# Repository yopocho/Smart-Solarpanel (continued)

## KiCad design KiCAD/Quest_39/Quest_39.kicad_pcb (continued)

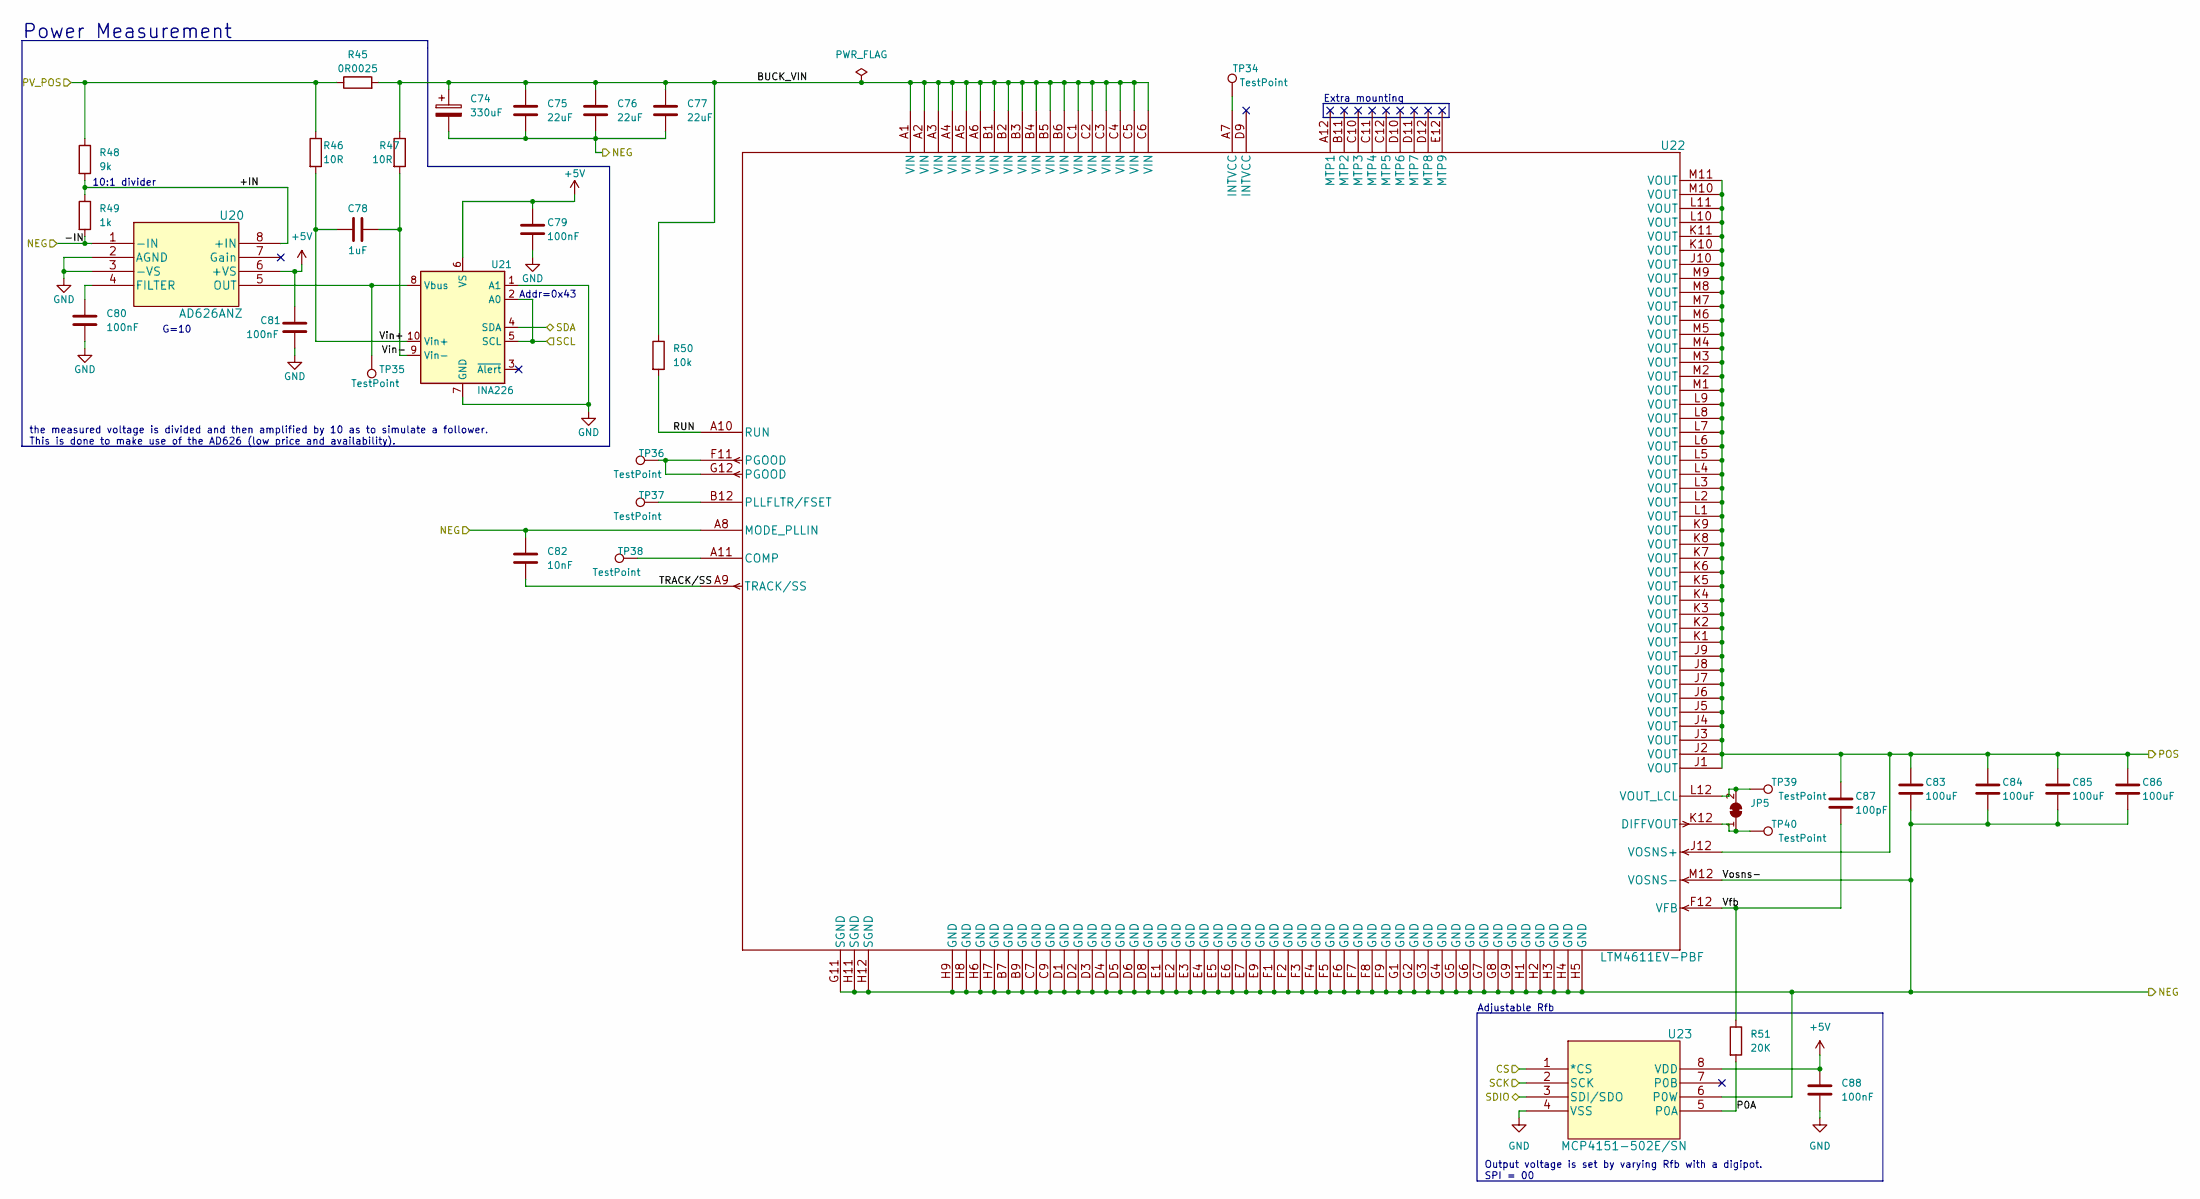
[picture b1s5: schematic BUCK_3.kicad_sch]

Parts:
C74: 330uF; CP_Elec_8x6.9
C75, C76, C77: 22uF; C_0805_2012Metric
C78: 1uF; C_0603_1608Metric
C79, C80, C81, C88: 100nF; C_0603_1608Metric
C82: 10nF; C_0603_1608Metric
C83, C84, C85, C86: 100uF; C_1206_3216Metric
C87: 100pF; C_0603_1608Metric
JP5: SolderJumper_2_Bridged; SolderJumper-2_P1.3mm_Bridged_RoundedPad1.0x1.5mm
R45: 0R0025; R_1206_3216Metric
R46, R47: 10R; R_0805_2012Metric
R48: 9k; R_0805_2012Metric
R49: 1k; R_0805_2012Metric
R50: 10k; R_0805_2012Metric
R51: 20K; R_0805_2012Metric
TP34, TP35, TP36, TP37, TP38, TP39, TP40: TestPoint; TestPoint_Pad_D2.0mm
U20: AD626ANZ; DIP-8_W7.62mm_Socket_LongPads
U21: INA226; VSSOP-10_3x3mm_P0.5mm
U22: LTM4611EV-PBF; Linear_LGA-133_15.0x15.0mm_Layout12x12_P1.27mm
U23: MCP4151-502E/SN; MSOP-8_3x3mm_P0.65mm

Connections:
+5V: C79.1, C81.1, C88.1, U20.6 (+VS), U21.6 (VS), U23.8 (VDD); also elsewhere on the board
/BUCK_3/+IN: R48.2, R49.1, U20.8 (+IN)
/BUCK_3/BUCK_VIN: C74.1, C75.1, C76.1, C77.1, R45.2, R47.1, R50.1, U22.A1 (VIN), U22.A2 (VIN), U22.A3 (VIN), U22.A4 (VIN), U22.A5 (VIN), U22.A6 (VIN), U22.B1 (VIN), U22.B2 (VIN), U22.B3 (VIN), U22.B4 (VIN), U22.B5 (VIN), U22.B6 (VIN), U22.C1 (VIN), U22.C2 (VIN), U22.C3 (VIN), U22.C4 (VIN), U22.C5 (VIN), U22.C6 (VIN)
/BUCK_3/P0A: R51.2, U23.5 (P0A)
/BUCK_3/RUN: R50.2, U22.A10 (RUN)
/BUCK_3/TRACK/SS: C82.2, U22.A9 (TRACK/SS)
/BUCK_3/Vfb: C87.2, R51.1, U22.F12 (VFB)
/BUCK_3/Vin+: C78.1, R46.2, U21.10 (Vin+)
/BUCK_3/Vin-: C78.2, R47.2, U21.9 (Vin-)
/CS3: U23.1 (*CS); also elsewhere on the board
/NEG_3: C74.2, C75.2, C76.2, C77.2, C82.1, C83.2, C84.2, C85.2, C86.2, R49.2, U20.1 (-IN), U22.A8 (MODE_PLLIN), U22.B7 (GND), U22.B9 (GND), U22.C7 (GND), U22.C9 (GND), U22.D1 (GND), U22.D2 (GND), U22.D3 (GND), U22.D4 (GND), U22.D5 (GND), U22.D6 (GND), U22.D8 (GND), U22.E1 (GND), U22.E2 (GND), U22.E3 (GND), U22.E4 (GND), U22.E5 (GND), U22.E6 (GND), U22.E7 (GND), U22.E9 (GND), U22.F1 (GND), U22.F2 (GND), U22.F3 (GND), U22.F4 (GND), U22.F5 (GND), U22.F6 (GND), U22.F7 (GND), U22.F8 (GND), U22.F9 (GND), U22.G1 (GND), U22.G2 (GND), U22.G3 (GND), U22.G4 (GND), U22.G5 (GND), U22.G6 (GND), U22.G7 (GND), U22.G8 (GND), U22.G9 (GND), U22.G11 (SGND), U22.H1 (GND), U22.H2 (GND), U22.H3 (GND), U22.H4 (GND), U22.H5 (GND), U22.H6 (GND), U22.H7 (GND), U22.H8 (GND), U22.H9 (GND), U22.H11 (SGND), U22.H12 (SGND), U22.M12 (VOSNS-), U23.6 (P0W); also elsewhere on the board
/NEG_4: C83.1, C84.1, C85.1, C86.1, C87.1, U22.J1 (VOUT), U22.J2 (VOUT), U22.J3 (VOUT), U22.J4 (VOUT), U22.J5 (VOUT), U22.J6 (VOUT), U22.J7 (VOUT), U22.J8 (VOUT), U22.J9 (VOUT), U22.J10 (VOUT), U22.J12 (VOSNS+), U22.K1 (VOUT), U22.K2 (VOUT), U22.K3 (VOUT), U22.K4 (VOUT), U22.K5 (VOUT), U22.K6 (VOUT), U22.K7 (VOUT), U22.K8 (VOUT), U22.K9 (VOUT), U22.K10 (VOUT), U22.K11 (VOUT), U22.L1 (VOUT), U22.L2 (VOUT), U22.L3 (VOUT), U22.L4 (VOUT), U22.L5 (VOUT), U22.L6 (VOUT), U22.L7 (VOUT), U22.L8 (VOUT), U22.L9 (VOUT), U22.L10 (VOUT), U22.L11 (VOUT), U22.M1 (VOUT), U22.M2 (VOUT), U22.M3 (VOUT), U22.M4 (VOUT), U22.M5 (VOUT), U22.M6 (VOUT), U22.M7 (VOUT), U22.M8 (VOUT), U22.M9 (VOUT), U22.M10 (VOUT), U22.M11 (VOUT); also elsewhere on the board
/PV_POS_3: R45.1, R46.1, R48.1; also elsewhere on the board
/SCK: U23.2 (SCK); also elsewhere on the board
/SCL: U21.2 (A0), U21.5 (SCL); also elsewhere on the board
/SDA: U21.4 (SDA); also elsewhere on the board
/SDIO: U23.3 (SDI/SDO); also elsewhere on the board
GND: C79.2, C80.2, C81.2, C88.2, U20.2 (AGND), U20.3 (-VS), U21.1 (A1), U21.7 (GND), U23.4 (VSS); also elsewhere on the board
unnamed: C80.1, U20.4 (FILTER)
unnamed: JP5.1 (A), TP40.1, U22.K12 (DIFFVOUT)
unnamed: JP5.2 (B), TP39.1, U22.L12 (VOUT_LCL)
unnamed: TP34.1, U22.A7 (INTVCC)
unnamed: TP35.1, U20.5 (OUT), U21.8 (Vbus)
unnamed: TP36.1, U22.F11 (PGOOD), U22.G12 (PGOOD)
unnamed: TP37.1, U22.B12 (PLLFLTR/FSET)
unnamed: TP38.1, U22.A11 (COMP)

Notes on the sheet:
Adjustable Rfb
the measured voltage is divided and then amplified by 10 as to simulate a follower. This is done to make use of the AD626 (low price and availability).
Extra mounting
Output voltage is set by varying Rfb with a digipot. SPI = 00
Addr=0x43
10:1 divider
G=10
Power Measurement

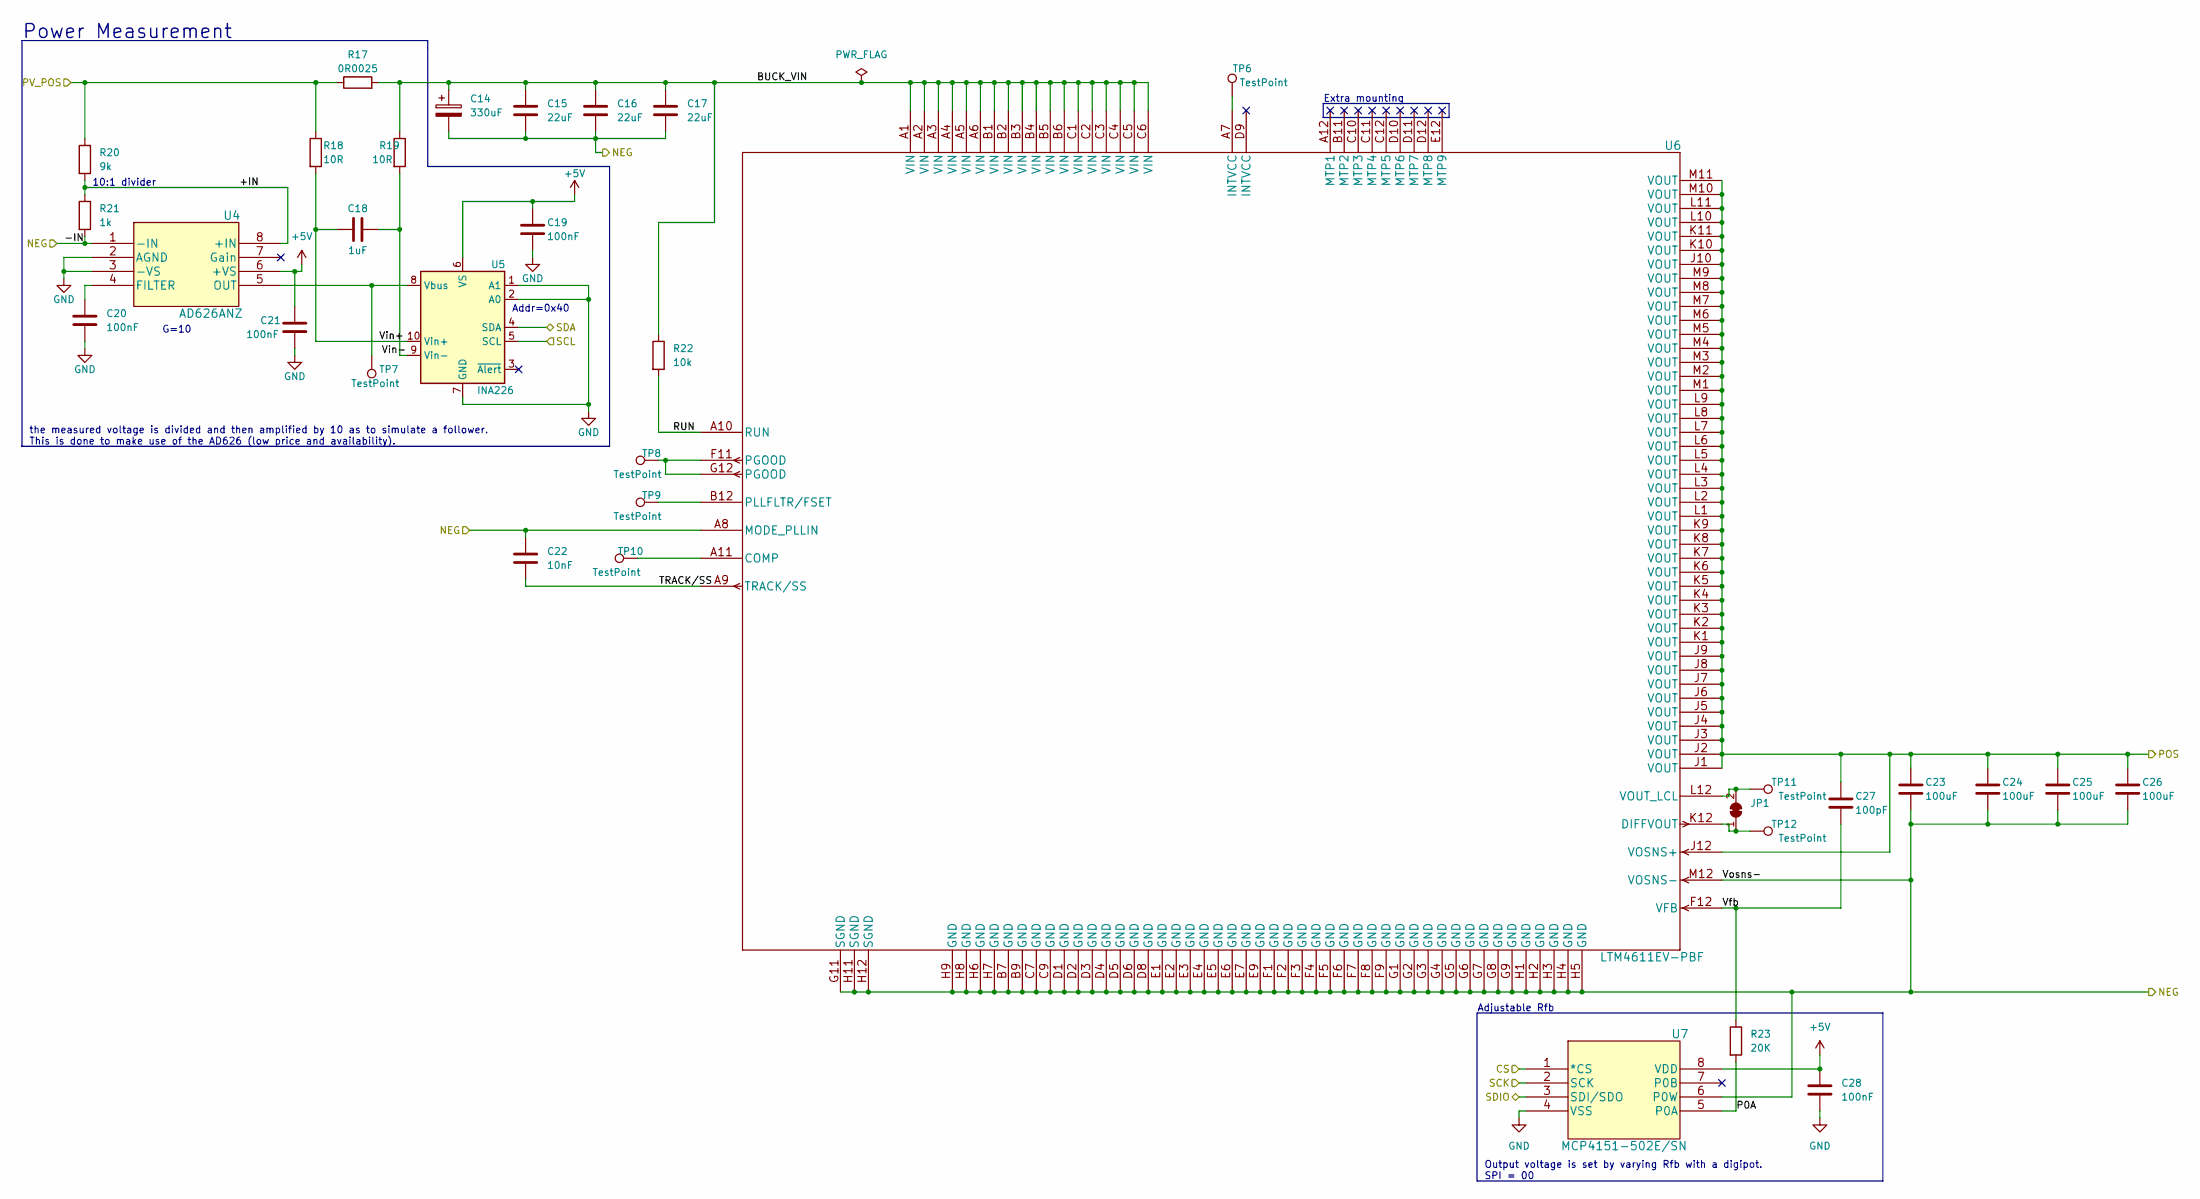
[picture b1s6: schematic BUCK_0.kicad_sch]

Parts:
C14: 330uF; CP_Elec_8x6.9
C15, C16, C17: 22uF; C_0805_2012Metric
C18: 1uF; C_0603_1608Metric
C19, C20, C21, C28: 100nF; C_0603_1608Metric
C22: 10nF; C_0603_1608Metric
C23, C24, C25, C26: 100uF; C_1206_3216Metric
C27: 100pF; C_0603_1608Metric
JP1: SolderJumper_2_Bridged; SolderJumper-2_P1.3mm_Bridged_RoundedPad1.0x1.5mm
R17: 0R0025; R_1206_3216Metric
R18, R19: 10R; R_0805_2012Metric
R20: 9k; R_0805_2012Metric
R21: 1k; R_0805_2012Metric
R22: 10k; R_0805_2012Metric
R23: 20K; R_0805_2012Metric
TP6, TP7, TP8, TP9, TP10, TP11, TP12: TestPoint; TestPoint_Pad_D2.0mm
U4: AD626ANZ; DIP-8_W7.62mm_Socket_LongPads
U5: INA226; VSSOP-10_3x3mm_P0.5mm
U6: LTM4611EV-PBF; Linear_LGA-133_15.0x15.0mm_Layout12x12_P1.27mm
U7: MCP4151-502E/SN; MSOP-8_3x3mm_P0.65mm

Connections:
+5V: C19.1, C21.1, C28.1, U4.6 (+VS), U5.6 (VS), U7.8 (VDD); also elsewhere on the board
/BUCK_0/+IN: R20.2, R21.1, U4.8 (+IN)
/BUCK_0/BUCK_VIN: C14.1, C15.1, C16.1, C17.1, R17.2, R19.1, R22.1, U6.A1 (VIN), U6.A2 (VIN), U6.A3 (VIN), U6.A4 (VIN), U6.A5 (VIN), U6.A6 (VIN), U6.B1 (VIN), U6.B2 (VIN), U6.B3 (VIN), U6.B4 (VIN), U6.B5 (VIN), U6.B6 (VIN), U6.C1 (VIN), U6.C2 (VIN), U6.C3 (VIN), U6.C4 (VIN), U6.C5 (VIN), U6.C6 (VIN)
/BUCK_0/P0A: R23.2, U7.5 (P0A)
/BUCK_0/RUN: R22.2, U6.A10 (RUN)
/BUCK_0/TRACK/SS: C22.2, U6.A9 (TRACK/SS)
/BUCK_0/Vfb: C27.2, R23.1, U6.F12 (VFB)
/BUCK_0/Vin+: C18.2, R18.2, U5.10 (Vin+)
/BUCK_0/Vin-: C18.1, R19.2, U5.9 (Vin-)
/CS0: U7.1 (*CS); also elsewhere on the board
/NEG_0: C14.2, C15.2, C16.2, C17.2, C22.1, C23.2, C24.2, C25.2, C26.2, R21.2, U4.1 (-IN), U6.A8 (MODE_PLLIN), U6.B7 (GND), U6.B9 (GND), U6.C7 (GND), U6.C9 (GND), U6.D1 (GND), U6.D2 (GND), U6.D3 (GND), U6.D4 (GND), U6.D5 (GND), U6.D6 (GND), U6.D8 (GND), U6.E1 (GND), U6.E2 (GND), U6.E3 (GND), U6.E4 (GND), U6.E5 (GND), U6.E6 (GND), U6.E7 (GND), U6.E9 (GND), U6.F1 (GND), U6.F2 (GND), U6.F3 (GND), U6.F4 (GND), U6.F5 (GND), U6.F6 (GND), U6.F7 (GND), U6.F8 (GND), U6.F9 (GND), U6.G1 (GND), U6.G2 (GND), U6.G3 (GND), U6.G4 (GND), U6.G5 (GND), U6.G6 (GND), U6.G7 (GND), U6.G8 (GND), U6.G9 (GND), U6.G11 (SGND), U6.H1 (GND), U6.H2 (GND), U6.H3 (GND), U6.H4 (GND), U6.H5 (GND), U6.H6 (GND), U6.H7 (GND), U6.H8 (GND), U6.H9 (GND), U6.H11 (SGND), U6.H12 (SGND), U6.M12 (VOSNS-), U7.6 (P0W); also elsewhere on the board
/NEG_1: C23.1, C24.1, C25.1, C26.1, C27.1, U6.J1 (VOUT), U6.J2 (VOUT), U6.J3 (VOUT), U6.J4 (VOUT), U6.J5 (VOUT), U6.J6 (VOUT), U6.J7 (VOUT), U6.J8 (VOUT), U6.J9 (VOUT), U6.J10 (VOUT), U6.J12 (VOSNS+), U6.K1 (VOUT), U6.K2 (VOUT), U6.K3 (VOUT), U6.K4 (VOUT), U6.K5 (VOUT), U6.K6 (VOUT), U6.K7 (VOUT), U6.K8 (VOUT), U6.K9 (VOUT), U6.K10 (VOUT), U6.K11 (VOUT), U6.L1 (VOUT), U6.L2 (VOUT), U6.L3 (VOUT), U6.L4 (VOUT), U6.L5 (VOUT), U6.L6 (VOUT), U6.L7 (VOUT), U6.L8 (VOUT), U6.L9 (VOUT), U6.L10 (VOUT), U6.L11 (VOUT), U6.M1 (VOUT), U6.M2 (VOUT), U6.M3 (VOUT), U6.M4 (VOUT), U6.M5 (VOUT), U6.M6 (VOUT), U6.M7 (VOUT), U6.M8 (VOUT), U6.M9 (VOUT), U6.M10 (VOUT), U6.M11 (VOUT); also elsewhere on the board
/PV_POS_0: R17.1, R18.1, R20.1; also elsewhere on the board
/SCK: U7.2 (SCK); also elsewhere on the board
/SCL: U5.5 (SCL); also elsewhere on the board
/SDA: U5.4 (SDA); also elsewhere on the board
/SDIO: U7.3 (SDI/SDO); also elsewhere on the board
GND: C19.2, C20.2, C21.2, C28.2, U4.2 (AGND), U4.3 (-VS), U5.1 (A1), U5.2 (A0), U5.7 (GND), U7.4 (VSS); also elsewhere on the board
unnamed: C20.1, U4.4 (FILTER)
unnamed: JP1.1 (A), TP12.1, U6.K12 (DIFFVOUT)
unnamed: JP1.2 (B), TP11.1, U6.L12 (VOUT_LCL)
unnamed: TP6.1, U6.A7 (INTVCC)
unnamed: TP7.1, U4.5 (OUT), U5.8 (Vbus)
unnamed: TP8.1, U6.F11 (PGOOD), U6.G12 (PGOOD)
unnamed: TP9.1, U6.B12 (PLLFLTR/FSET)
unnamed: TP10.1, U6.A11 (COMP)

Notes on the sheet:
Addr=0x40
10:1 divider
the measured voltage is divided and then amplified by 10 as to simulate a follower. This is done to make use of the AD626 (low price and availability).
Power Measurement
Output voltage is set by varying Rfb with a digipot. SPI = 00
Adjustable Rfb
Extra mounting
G=10

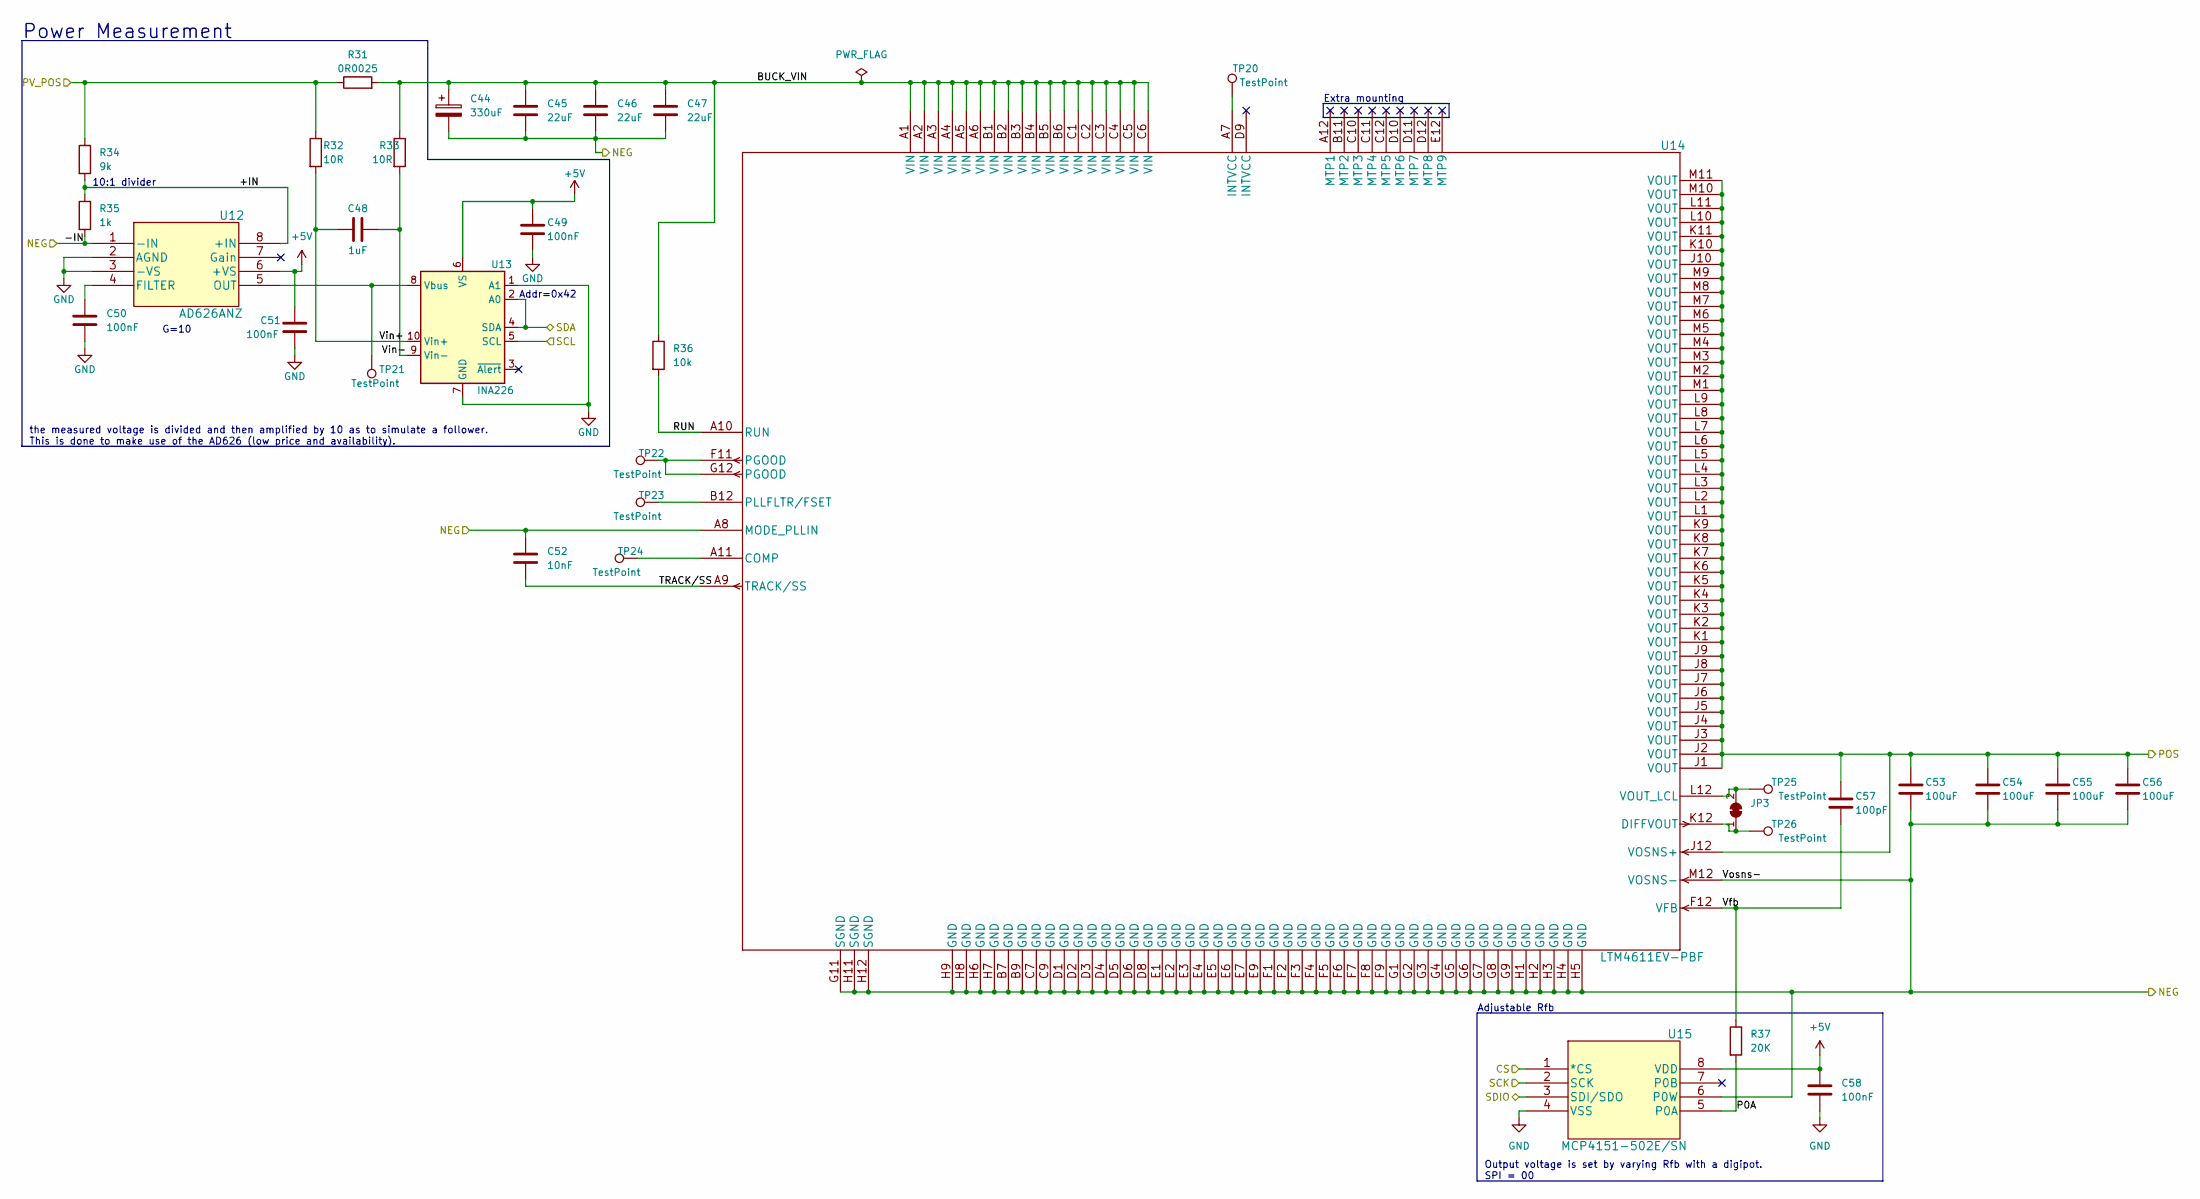
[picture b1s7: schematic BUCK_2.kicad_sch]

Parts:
C44: 330uF; CP_Elec_8x6.9
C45, C46, C47: 22uF; C_0805_2012Metric
C48: 1uF; C_0603_1608Metric
C49, C50, C51, C58: 100nF; C_0603_1608Metric
C52: 10nF; C_0603_1608Metric
C53, C54, C55, C56: 100uF; C_1206_3216Metric
C57: 100pF; C_0603_1608Metric
JP3: SolderJumper_2_Bridged; SolderJumper-2_P1.3mm_Bridged_RoundedPad1.0x1.5mm
R31: 0R0025; R_1206_3216Metric
R32, R33: 10R; R_0805_2012Metric
R34: 9k; R_0805_2012Metric
R35: 1k; R_0805_2012Metric
R36: 10k; R_0805_2012Metric
R37: 20K; R_0805_2012Metric
TP20, TP21, TP22, TP23, TP24, TP25, TP26: TestPoint; TestPoint_Pad_D2.0mm
U12: AD626ANZ; DIP-8_W7.62mm_Socket_LongPads
U13: INA226; VSSOP-10_3x3mm_P0.5mm
U14: LTM4611EV-PBF; Linear_LGA-133_15.0x15.0mm_Layout12x12_P1.27mm
U15: MCP4151-502E/SN; MSOP-8_3x3mm_P0.65mm

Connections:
+5V: C49.1, C51.1, C58.1, U12.6 (+VS), U13.6 (VS), U15.8 (VDD); also elsewhere on the board
/BUCK_2/+IN: R34.2, R35.1, U12.8 (+IN)
/BUCK_2/BUCK_VIN: C44.1, C45.1, C46.1, C47.1, R31.2, R33.1, R36.1, U14.A1 (VIN), U14.A2 (VIN), U14.A3 (VIN), U14.A4 (VIN), U14.A5 (VIN), U14.A6 (VIN), U14.B1 (VIN), U14.B2 (VIN), U14.B3 (VIN), U14.B4 (VIN), U14.B5 (VIN), U14.B6 (VIN), U14.C1 (VIN), U14.C2 (VIN), U14.C3 (VIN), U14.C4 (VIN), U14.C5 (VIN), U14.C6 (VIN)
/BUCK_2/P0A: R37.2, U15.5 (P0A)
/BUCK_2/RUN: R36.2, U14.A10 (RUN)
/BUCK_2/TRACK/SS: C52.2, U14.A9 (TRACK/SS)
/BUCK_2/Vfb: C57.2, R37.1, U14.F12 (VFB)
/BUCK_2/Vin+: C48.1, R32.2, U13.10 (Vin+)
/BUCK_2/Vin-: C48.2, R33.2, U13.9 (Vin-)
/CS2: U15.1 (*CS); also elsewhere on the board
/NEG_2: C44.2, C45.2, C46.2, C47.2, C52.1, C53.2, C54.2, C55.2, C56.2, R35.2, U12.1 (-IN), U14.A8 (MODE_PLLIN), U14.B7 (GND), U14.B9 (GND), U14.C7 (GND), U14.C9 (GND), U14.D1 (GND), U14.D2 (GND), U14.D3 (GND), U14.D4 (GND), U14.D5 (GND), U14.D6 (GND), U14.D8 (GND), U14.E1 (GND), U14.E2 (GND), U14.E3 (GND), U14.E4 (GND), U14.E5 (GND), U14.E6 (GND), U14.E7 (GND), U14.E9 (GND), U14.F1 (GND), U14.F2 (GND), U14.F3 (GND), U14.F4 (GND), U14.F5 (GND), U14.F6 (GND), U14.F7 (GND), U14.F8 (GND), U14.F9 (GND), U14.G1 (GND), U14.G2 (GND), U14.G3 (GND), U14.G4 (GND), U14.G5 (GND), U14.G6 (GND), U14.G7 (GND), U14.G8 (GND), U14.G9 (GND), U14.G11 (SGND), U14.H1 (GND), U14.H2 (GND), U14.H3 (GND), U14.H4 (GND), U14.H5 (GND), U14.H6 (GND), U14.H7 (GND), U14.H8 (GND), U14.H9 (GND), U14.H11 (SGND), U14.H12 (SGND), U14.M12 (VOSNS-), U15.6 (P0W); also elsewhere on the board
/NEG_3: C53.1, C54.1, C55.1, C56.1, C57.1, U14.J1 (VOUT), U14.J2 (VOUT), U14.J3 (VOUT), U14.J4 (VOUT), U14.J5 (VOUT), U14.J6 (VOUT), U14.J7 (VOUT), U14.J8 (VOUT), U14.J9 (VOUT), U14.J10 (VOUT), U14.J12 (VOSNS+), U14.K1 (VOUT), U14.K2 (VOUT), U14.K3 (VOUT), U14.K4 (VOUT), U14.K5 (VOUT), U14.K6 (VOUT), U14.K7 (VOUT), U14.K8 (VOUT), U14.K9 (VOUT), U14.K10 (VOUT), U14.K11 (VOUT), U14.L1 (VOUT), U14.L2 (VOUT), U14.L3 (VOUT), U14.L4 (VOUT), U14.L5 (VOUT), U14.L6 (VOUT), U14.L7 (VOUT), U14.L8 (VOUT), U14.L9 (VOUT), U14.L10 (VOUT), U14.L11 (VOUT), U14.M1 (VOUT), U14.M2 (VOUT), U14.M3 (VOUT), U14.M4 (VOUT), U14.M5 (VOUT), U14.M6 (VOUT), U14.M7 (VOUT), U14.M8 (VOUT), U14.M9 (VOUT), U14.M10 (VOUT), U14.M11 (VOUT); also elsewhere on the board
/PV_POS_2: R31.1, R32.1, R34.1; also elsewhere on the board
/SCK: U15.2 (SCK); also elsewhere on the board
/SCL: U13.5 (SCL); also elsewhere on the board
/SDA: U13.2 (A0), U13.4 (SDA); also elsewhere on the board
/SDIO: U15.3 (SDI/SDO); also elsewhere on the board
GND: C49.2, C50.2, C51.2, C58.2, U12.2 (AGND), U12.3 (-VS), U13.1 (A1), U13.7 (GND), U15.4 (VSS); also elsewhere on the board
unnamed: C50.1, U12.4 (FILTER)
unnamed: JP3.1 (A), TP26.1, U14.K12 (DIFFVOUT)
unnamed: JP3.2 (B), TP25.1, U14.L12 (VOUT_LCL)
unnamed: TP20.1, U14.A7 (INTVCC)
unnamed: TP21.1, U12.5 (OUT), U13.8 (Vbus)
unnamed: TP22.1, U14.F11 (PGOOD), U14.G12 (PGOOD)
unnamed: TP23.1, U14.B12 (PLLFLTR/FSET)
unnamed: TP24.1, U14.A11 (COMP)

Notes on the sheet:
the measured voltage is divided and then amplified by 10 as to simulate a follower. This is done to make use of the AD626 (low price and availability).
Extra mounting
G=10
10:1 divider
Adjustable Rfb
Addr=0x42
Output voltage is set by varying Rfb with a digipot. SPI = 00
Power Measurement

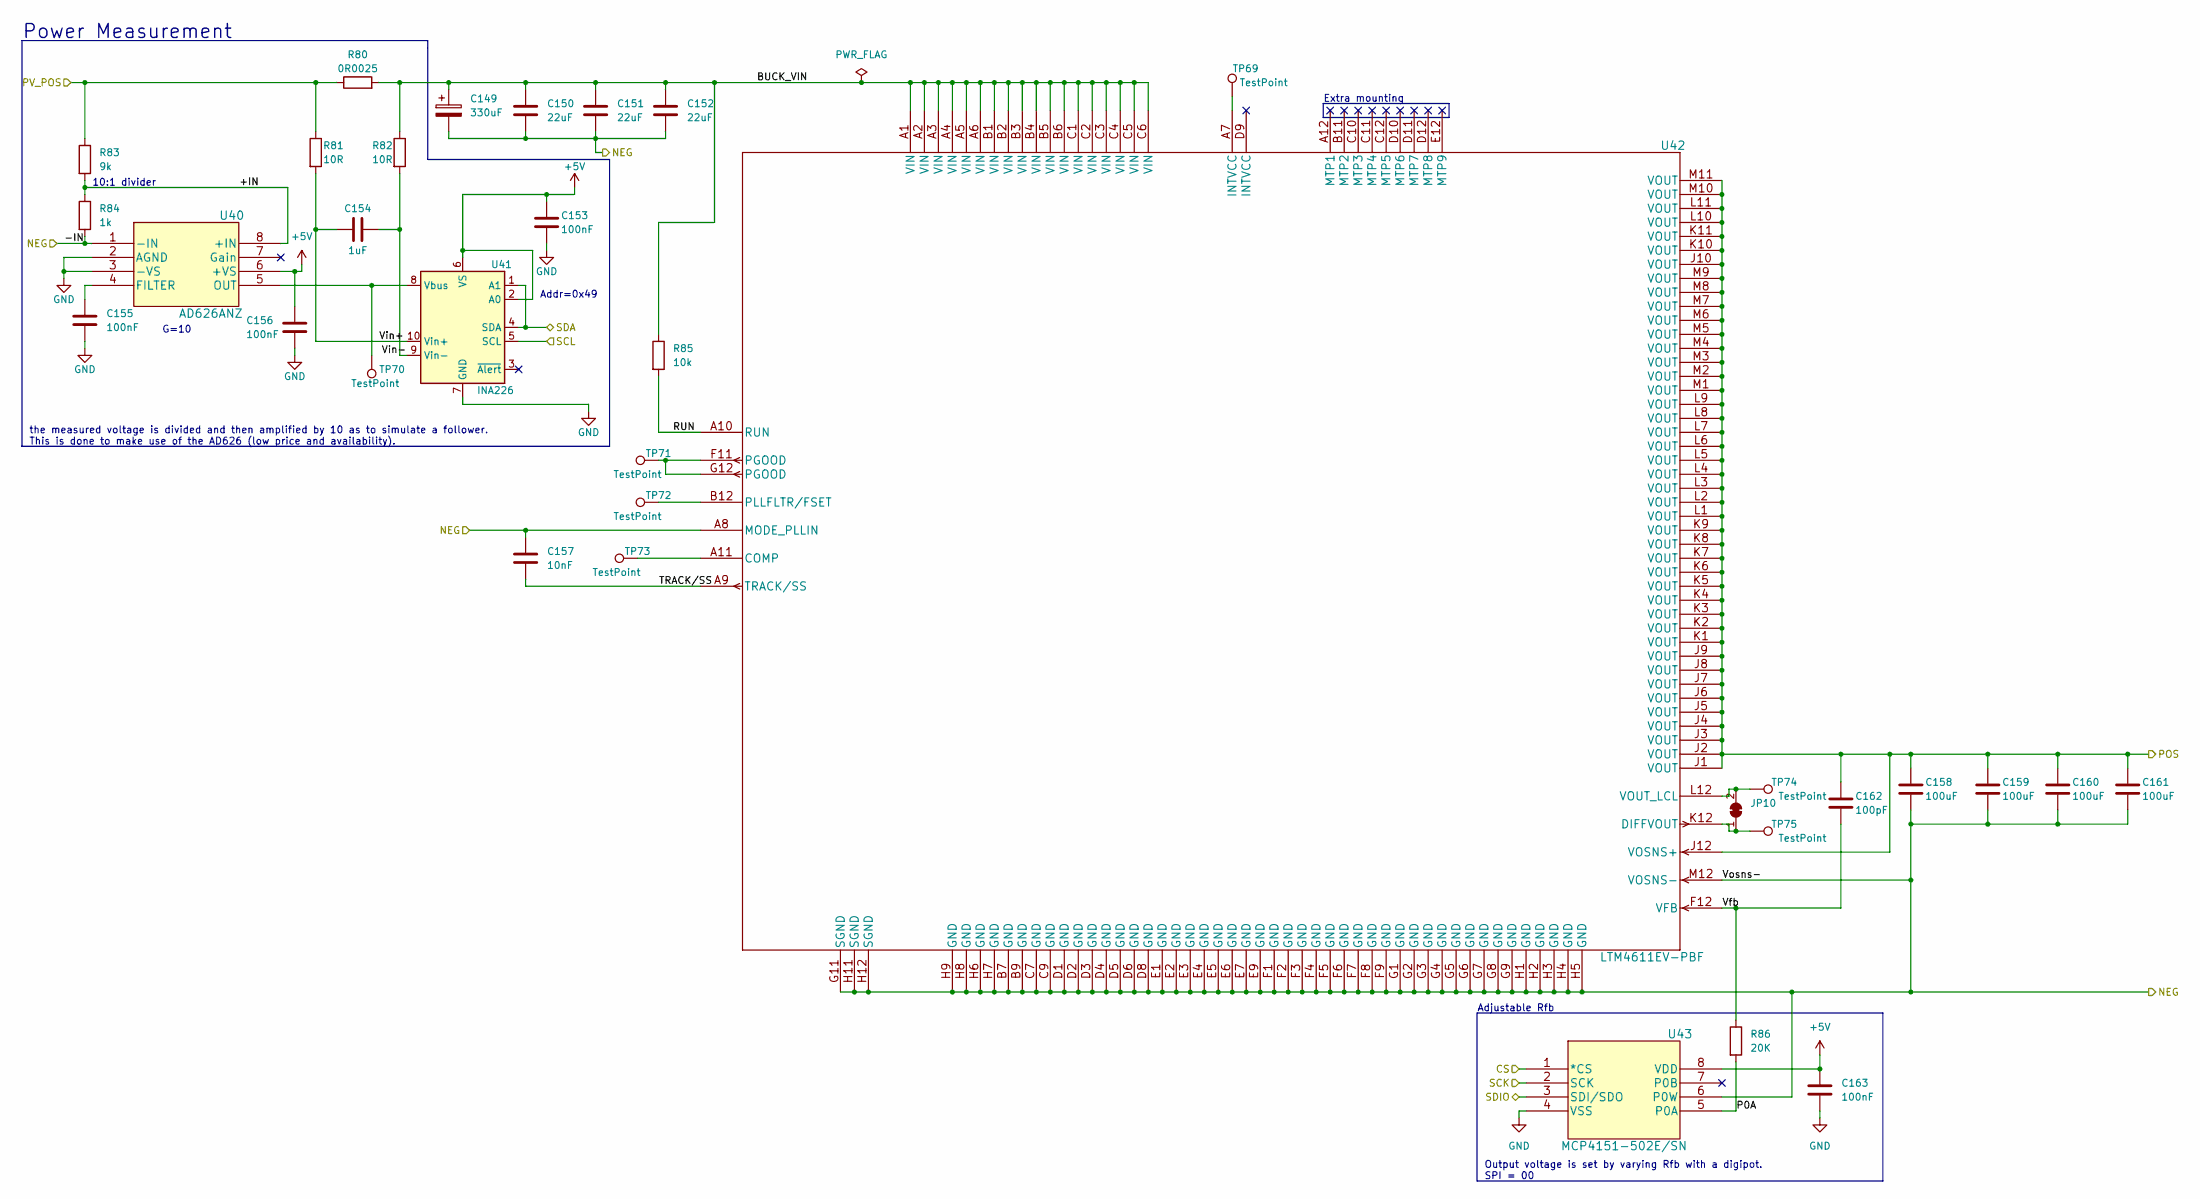
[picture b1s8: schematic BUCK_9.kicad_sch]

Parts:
C149: 330uF; CP_Elec_8x6.9
C150, C151, C152: 22uF; C_0805_2012Metric
C153, C155, C156, C163: 100nF; C_0603_1608Metric
C154: 1uF; C_0603_1608Metric
C157: 10nF; C_0603_1608Metric
C158, C159, C160, C161: 100uF; C_1206_3216Metric
C162: 100pF; C_0603_1608Metric
JP10: SolderJumper_2_Bridged; SolderJumper-2_P1.3mm_Bridged_RoundedPad1.0x1.5mm
R80: 0R0025; R_1206_3216Metric
R81, R82: 10R; R_0805_2012Metric
R83: 9k; R_0805_2012Metric
R84: 1k; R_0805_2012Metric
R85: 10k; R_0805_2012Metric
R86: 20K; R_0805_2012Metric
TP69, TP70, TP71, TP72, TP73, TP74, TP75: TestPoint; TestPoint_Pad_D2.0mm
U40: AD626ANZ; DIP-8_W7.62mm_Socket_LongPads
U41: INA226; VSSOP-10_3x3mm_P0.5mm
U42: LTM4611EV-PBF; Linear_LGA-133_15.0x15.0mm_Layout12x12_P1.27mm
U43: MCP4151-502E/SN; MSOP-8_3x3mm_P0.65mm

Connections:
+5V: C153.1, C156.1, C163.1, U40.6 (+VS), U41.2 (A0), U41.6 (VS), U43.8 (VDD); also elsewhere on the board
/BUCK_9/+IN: R83.2, R84.1, U40.8 (+IN)
/BUCK_9/BUCK_VIN: C149.1, C150.1, C151.1, C152.1, R80.2, R82.1, R85.1, U42.A1 (VIN), U42.A2 (VIN), U42.A3 (VIN), U42.A4 (VIN), U42.A5 (VIN), U42.A6 (VIN), U42.B1 (VIN), U42.B2 (VIN), U42.B3 (VIN), U42.B4 (VIN), U42.B5 (VIN), U42.B6 (VIN), U42.C1 (VIN), U42.C2 (VIN), U42.C3 (VIN), U42.C4 (VIN), U42.C5 (VIN), U42.C6 (VIN)
/BUCK_9/P0A: R86.2, U43.5 (P0A)
/BUCK_9/RUN: R85.2, U42.A10 (RUN)
/BUCK_9/TRACK/SS: C157.2, U42.A9 (TRACK/SS)
/BUCK_9/Vfb: C162.2, R86.1, U42.F12 (VFB)
/BUCK_9/Vin+: C154.1, R81.2, U41.10 (Vin+)
/BUCK_9/Vin-: C154.2, R82.2, U41.9 (Vin-)
/CS9: U43.1 (*CS); also elsewhere on the board
/NEG_9: C149.2, C150.2, C151.2, C152.2, C157.1, C158.2, C159.2, C160.2, C161.2, R84.2, U40.1 (-IN), U42.A8 (MODE_PLLIN), U42.B7 (GND), U42.B9 (GND), U42.C7 (GND), U42.C9 (GND), U42.D1 (GND), U42.D2 (GND), U42.D3 (GND), U42.D4 (GND), U42.D5 (GND), U42.D6 (GND), U42.D8 (GND), U42.E1 (GND), U42.E2 (GND), U42.E3 (GND), U42.E4 (GND), U42.E5 (GND), U42.E6 (GND), U42.E7 (GND), U42.E9 (GND), U42.F1 (GND), U42.F2 (GND), U42.F3 (GND), U42.F4 (GND), U42.F5 (GND), U42.F6 (GND), U42.F7 (GND), U42.F8 (GND), U42.F9 (GND), U42.G1 (GND), U42.G2 (GND), U42.G3 (GND), U42.G4 (GND), U42.G5 (GND), U42.G6 (GND), U42.G7 (GND), U42.G8 (GND), U42.G9 (GND), U42.G11 (SGND), U42.H1 (GND), U42.H2 (GND), U42.H3 (GND), U42.H4 (GND), U42.H5 (GND), U42.H6 (GND), U42.H7 (GND), U42.H8 (GND), U42.H9 (GND), U42.H11 (SGND), U42.H12 (SGND), U42.M12 (VOSNS-), U43.6 (P0W); also elsewhere on the board
/POS_9: C158.1, C159.1, C160.1, C161.1, C162.1, U42.J1 (VOUT), U42.J2 (VOUT), U42.J3 (VOUT), U42.J4 (VOUT), U42.J5 (VOUT), U42.J6 (VOUT), U42.J7 (VOUT), U42.J8 (VOUT), U42.J9 (VOUT), U42.J10 (VOUT), U42.J12 (VOSNS+), U42.K1 (VOUT), U42.K2 (VOUT), U42.K3 (VOUT), U42.K4 (VOUT), U42.K5 (VOUT), U42.K6 (VOUT), U42.K7 (VOUT), U42.K8 (VOUT), U42.K9 (VOUT), U42.K10 (VOUT), U42.K11 (VOUT), U42.L1 (VOUT), U42.L2 (VOUT), U42.L3 (VOUT), U42.L4 (VOUT), U42.L5 (VOUT), U42.L6 (VOUT), U42.L7 (VOUT), U42.L8 (VOUT), U42.L9 (VOUT), U42.L10 (VOUT), U42.L11 (VOUT), U42.M1 (VOUT), U42.M2 (VOUT), U42.M3 (VOUT), U42.M4 (VOUT), U42.M5 (VOUT), U42.M6 (VOUT), U42.M7 (VOUT), U42.M8 (VOUT), U42.M9 (VOUT), U42.M10 (VOUT), U42.M11 (VOUT); also elsewhere on the board
/PV_POS_9: R80.1, R81.1, R83.1; also elsewhere on the board
/SCK: U43.2 (SCK); also elsewhere on the board
/SCL: U41.5 (SCL); also elsewhere on the board
/SDA: U41.1 (A1), U41.4 (SDA); also elsewhere on the board
/SDIO: U43.3 (SDI/SDO); also elsewhere on the board
GND: C153.2, C155.2, C156.2, C163.2, U40.2 (AGND), U40.3 (-VS), U41.7 (GND), U43.4 (VSS); also elsewhere on the board
unnamed: C155.1, U40.4 (FILTER)
unnamed: JP10.1 (A), TP75.1, U42.K12 (DIFFVOUT)
unnamed: JP10.2 (B), TP74.1, U42.L12 (VOUT_LCL)
unnamed: TP69.1, U42.A7 (INTVCC)
unnamed: TP70.1, U40.5 (OUT), U41.8 (Vbus)
unnamed: TP71.1, U42.F11 (PGOOD), U42.G12 (PGOOD)
unnamed: TP72.1, U42.B12 (PLLFLTR/FSET)
unnamed: TP73.1, U42.A11 (COMP)

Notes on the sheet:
Adjustable Rfb
Output voltage is set by varying Rfb with a digipot. SPI = 00
10:1 divider
Addr=0x49
G=10
Extra mounting
the measured voltage is divided and then amplified by 10 as to simulate a follower. This is done to make use of the AD626 (low price and availability).
Power Measurement

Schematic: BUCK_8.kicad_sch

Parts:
C134: 330uF; CP_Elec_8x6.9
C135, C136, C137: 22uF; C_0805_2012Metric
C138, C140, C141, C148: 100nF; C_0603_1608Metric
C139: 1uF; C_0603_1608Metric
C142: 10nF; C_0603_1608Metric
C143, C144, C145, C146: 100uF; C_1206_3216Metric
C147: 100pF; C_0603_1608Metric
JP9: SolderJumper_2_Bridged; SolderJumper-2_P1.3mm_Bridged_RoundedPad1.0x1.5mm
R73: 0R0025; R_1206_3216Metric
R74, R75: 10R; R_0805_2012Metric
R76: 9k; R_0805_2012Metric
R77: 1k; R_0805_2012Metric
R78: 10k; R_0805_2012Metric
R79: 20K; R_0805_2012Metric
TP62, TP63, TP64, TP65, TP66, TP67, TP68: TestPoint; TestPoint_Pad_D2.0mm
U36: AD626ANZ; DIP-8_W7.62mm_Socket_LongPads
U37: INA226; VSSOP-10_3x3mm_P0.5mm
U38: LTM4611EV-PBF; Linear_LGA-133_15.0x15.0mm_Layout12x12_P1.27mm
U39: MCP4151-502E/SN; MSOP-8_3x3mm_P0.65mm

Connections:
+5V: C138.1, C141.1, C148.1, U36.6 (+VS), U37.6 (VS), U39.8 (VDD); also elsewhere on the board
/BUCK_8/+IN: R76.2, R77.1, U36.8 (+IN)
/BUCK_8/BUCK_VIN: C134.1, C135.1, C136.1, C137.1, R73.2, R75.1, R78.1, U38.A1 (VIN), U38.A2 (VIN), U38.A3 (VIN), U38.A4 (VIN), U38.A5 (VIN), U38.A6 (VIN), U38.B1 (VIN), U38.B2 (VIN), U38.B3 (VIN), U38.B4 (VIN), U38.B5 (VIN), U38.B6 (VIN), U38.C1 (VIN), U38.C2 (VIN), U38.C3 (VIN), U38.C4 (VIN), U38.C5 (VIN), U38.C6 (VIN)
/BUCK_8/P0A: R79.2, U39.5 (P0A)
/BUCK_8/RUN: R78.2, U38.A10 (RUN)
/BUCK_8/TRACK/SS: C142.2, U38.A9 (TRACK/SS)
/BUCK_8/Vfb: C147.2, R79.1, U38.F12 (VFB)
/BUCK_8/Vin+: C139.1, R74.2, U37.10 (Vin+)
/BUCK_8/Vin-: C139.2, R75.2, U37.9 (Vin-)
/CS8: U39.1 (*CS); also elsewhere on the board
/NEG_8: C134.2, C135.2, C136.2, C137.2, C142.1, C143.2, C144.2, C145.2, C146.2, R77.2, U36.1 (-IN), U38.A8 (MODE_PLLIN), U38.B7 (GND), U38.B9 (GND), U38.C7 (GND), U38.C9 (GND), U38.D1 (GND), U38.D2 (GND), U38.D3 (GND), U38.D4 (GND), U38.D5 (GND), U38.D6 (GND), U38.D8 (GND), U38.E1 (GND), U38.E2 (GND), U38.E3 (GND), U38.E4 (GND), U38.E5 (GND), U38.E6 (GND), U38.E7 (GND), U38.E9 (GND), U38.F1 (GND), U38.F2 (GND), U38.F3 (GND), U38.F4 (GND), U38.F5 (GND), U38.F6 (GND), U38.F7 (GND), U38.F8 (GND), U38.F9 (GND), U38.G1 (GND), U38.G2 (GND), U38.G3 (GND), U38.G4 (GND), U38.G5 (GND), U38.G6 (GND), U38.G7 (GND), U38.G8 (GND), U38.G9 (GND), U38.G11 (SGND), U38.H1 (GND), U38.H2 (GND), U38.H3 (GND), U38.H4 (GND), U38.H5 (GND), U38.H6 (GND), U38.H7 (GND), U38.H8 (GND), U38.H9 (GND), U38.H11 (SGND), U38.H12 (SGND), U38.M12 (VOSNS-), U39.6 (P0W); also elsewhere on the board
/NEG_9: C143.1, C144.1, C145.1, C146.1, C147.1, U38.J1 (VOUT), U38.J2 (VOUT), U38.J3 (VOUT), U38.J4 (VOUT), U38.J5 (VOUT), U38.J6 (VOUT), U38.J7 (VOUT), U38.J8 (VOUT), U38.J9 (VOUT), U38.J10 (VOUT), U38.J12 (VOSNS+), U38.K1 (VOUT), U38.K2 (VOUT), U38.K3 (VOUT), U38.K4 (VOUT), U38.K5 (VOUT), U38.K6 (VOUT), U38.K7 (VOUT), U38.K8 (VOUT), U38.K9 (VOUT), U38.K10 (VOUT), U38.K11 (VOUT), U38.L1 (VOUT), U38.L2 (VOUT), U38.L3 (VOUT), U38.L4 (VOUT), U38.L5 (VOUT), U38.L6 (VOUT), U38.L7 (VOUT), U38.L8 (VOUT), U38.L9 (VOUT), U38.L10 (VOUT), U38.L11 (VOUT), U38.M1 (VOUT), U38.M2 (VOUT), U38.M3 (VOUT), U38.M4 (VOUT), U38.M5 (VOUT), U38.M6 (VOUT), U38.M7 (VOUT), U38.M8 (VOUT), U38.M9 (VOUT), U38.M10 (VOUT), U38.M11 (VOUT); also elsewhere on the board
/PV_POS_8: R73.1, R74.1, R76.1; also elsewhere on the board
/SCK: U39.2 (SCK); also elsewhere on the board
/SCL: U37.5 (SCL); also elsewhere on the board
/SDA: U37.1 (A1), U37.4 (SDA); also elsewhere on the board
/SDIO: U39.3 (SDI/SDO); also elsewhere on the board
GND: C138.2, C140.2, C141.2, C148.2, U36.2 (AGND), U36.3 (-VS), U37.2 (A0), U37.7 (GND), U39.4 (VSS); also elsewhere on the board
unnamed: C140.1, U36.4 (FILTER)
unnamed: JP9.1 (A), TP68.1, U38.K12 (DIFFVOUT)
unnamed: JP9.2 (B), TP67.1, U38.L12 (VOUT_LCL)
unnamed: TP62.1, U38.A7 (INTVCC)
unnamed: TP63.1, U36.5 (OUT), U37.8 (Vbus)
unnamed: TP64.1, U38.F11 (PGOOD), U38.G12 (PGOOD)
unnamed: TP65.1, U38.B12 (PLLFLTR/FSET)
unnamed: TP66.1, U38.A11 (COMP)

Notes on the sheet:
Addr=0x48
G=10
Power Measurement
the measured voltage is divided and then amplified by 10 as to simulate a follower. This is done to make use of the AD626 (low price and availability).
Adjustable Rfb
Extra mounting
Output voltage is set by varying Rfb with a digipot. SPI = 00
10:1 divider
